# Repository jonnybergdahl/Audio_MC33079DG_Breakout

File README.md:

# Audio_MC33079DG_Breakout

This is a breakout board for the ON Semiconductor MC33079DG chip, setup for an audio configuration.

According to the manufacturer:

The MC33078/9 series is a family of high quality monolithic
amplifiers employing Bipolar technology with innovative high
performance concepts for quality audio and data signal processing
applications

## Inputs
Name | Description
---- | ----
1R | Input 1 Right CHannel
1L | Input 2 Left Channel
G | Analog Ground
2R | Input 2 Right Channel
2L | Input 2 Left Channel
G | Analog Ground

## Outputs
Name | Description
---- | ----
1R | Output 1 Right CHannel
2L | Output 1 Left Channel
G  | Analog Ground
2R | Output 2 Right Channel
2L | Output 2 Left Channel
G | Analog Ground

## Power
Name | Description
---- | ----
VCC | 10-36V power
GND | Ground

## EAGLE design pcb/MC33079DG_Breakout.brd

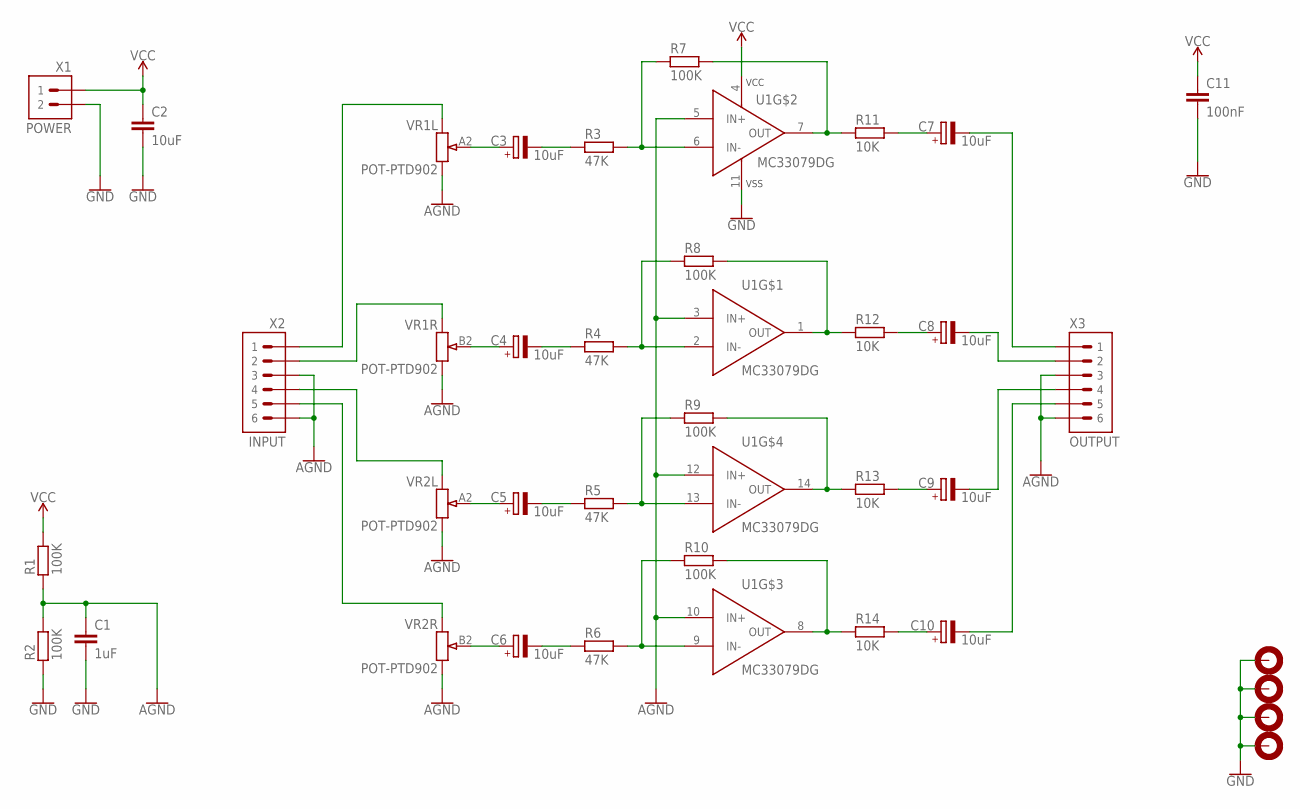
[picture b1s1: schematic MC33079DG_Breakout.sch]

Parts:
C1: 1uF; C0603
C2: 10uF; C0603
C3, C4, C5, C6, C7, C8, C9, C10: 10uF; ROQANG-RVT0405
C11: 100nF; C0603
H1, H2, H3, H4: MOUNTHOLE-PAD3.2; 3.2-PAD
R1, R2, R7, R8, R9, R10: 100K; R0603
R3, R4, R5, R6: 47K; R0603
R11, R12, R13, R14: 10K; R0603
U1: MC33079DG; SOIC-14
VR1, VR2: POT-PTD902
X1: POWER; 1X02P-2.54
X2: INPUT; 1X06-2.54
X3: OUTPUT; 1X06-2.54

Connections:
AGND: C1.1, R1.1, R2.2, U1.3 (IN+), U1.5 (IN+), U1.10 (IN+), U1.12 (IN+), VR1.A1 (1), VR1.B1 (1), VR2.A1 (1), VR2.B1 (1), X2.3, X2.6, X3.3, X3.6
GND: C1.2, C2.2, C11.2, H1.B3,2, H2.B3,2, H3.B3,2, H4.B3,2, R2.1, U1.11 (VSS), X1.2
unnamed: C3.-, R3.1
unnamed: R8.2, R12.1, U1.1 (OUT)
unnamed: C7.+, R11.2
unnamed: C8.+, R12.2
unnamed: R4.2, R8.1, U1.2 (IN-)
unnamed: R6.2, R10.1, U1.9 (IN-)
unnamed: R7.2, R11.1, U1.7 (OUT)
unnamed: R3.2, R7.1, U1.6 (IN-)
unnamed: C3.+, VR1.A2 (2)
unnamed: C4.-, R4.1
unnamed: C4.+, VR1.B2 (2)
unnamed: C5.+, VR2.A2 (2)
unnamed: C6.+, VR2.B2 (2)
unnamed: R5.2, R9.1, U1.13 (IN-)
unnamed: R9.2, R13.1, U1.14 (OUT)
unnamed: R10.2, R14.1, U1.8 (OUT)
unnamed: C10.+, R14.2
unnamed: C9.+, R13.2
unnamed: VR1.A3 (3), X2.1
unnamed: VR1.B3 (3), X2.2
unnamed: VR2.A3 (3), X2.4
unnamed: VR2.B3 (3), X2.5
unnamed: C7.-, X3.1
unnamed: C8.-, X3.2
unnamed: C9.-, X3.4
unnamed: C10.-, X3.5
unnamed: C5.-, R5.1
unnamed: C6.-, R6.1
VCC: C2.1, C11.1, R1.2, U1.4 (VCC), X1.1

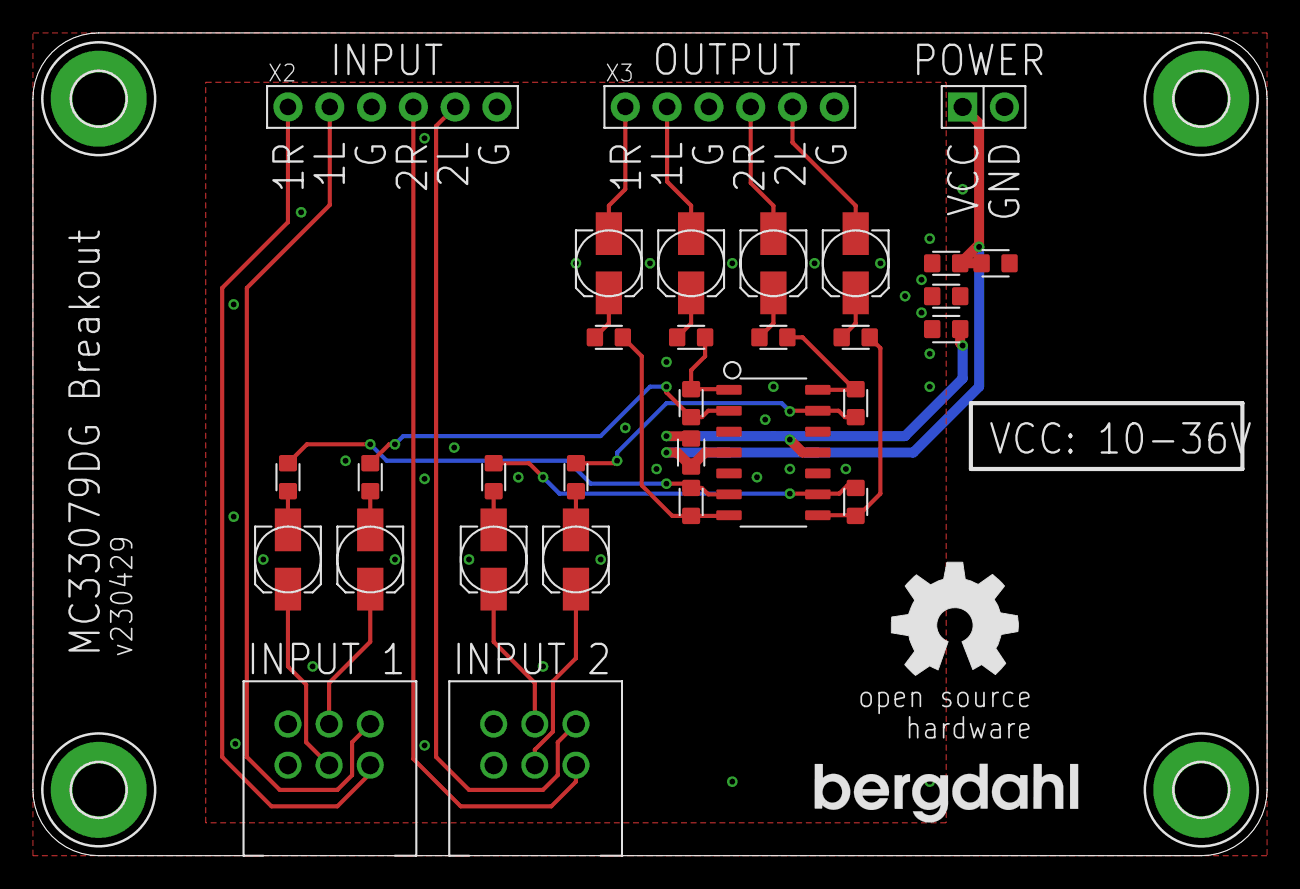
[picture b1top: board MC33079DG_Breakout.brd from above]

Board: 2 copper layers, 75.0 x 50.0 mm, 39 parts (0 on the bottom side), 31 nets.

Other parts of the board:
U$1: BERGDAHL-20MM-BPLACE
U$2: OSHW-8MM-BPLACE
U$3: BERGDAHL-20MM-TPLACE
U$5: OSHW-8MM-TPLACE

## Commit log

2023-05-08 Add Gerber files
